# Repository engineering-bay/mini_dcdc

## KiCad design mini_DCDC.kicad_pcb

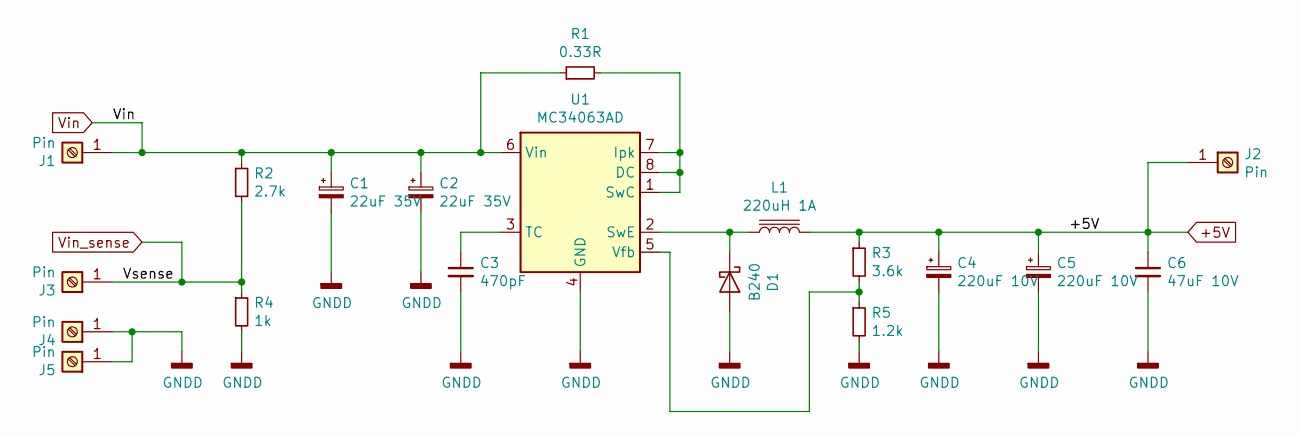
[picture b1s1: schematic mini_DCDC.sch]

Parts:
C1, C2: 22uF 35V; CP_EIA-7343-31_Kemet-D_Pad2.25x2.55mm_HandSolder; partnum 293D226X9035D2TE3
C3: 470pF; C_0805_2012Metric_Pad1.15x1.40mm_HandSolder; partnum CC0805JRNPO9BN471
C4, C5: 220uF 10V; CP_EIA-7343-31_Kemet-D_Pad2.25x2.55mm_HandSolder; partnum 293D227X9010D2TE3
C6: 47uF 10V; C_1206_3216Metric_Pad1.42x1.75mm_HandSolder; partnum GRM31CR61A476ME15L
D1: B240; D_SMB
J1, J2, J3, J4, J5: Pin; TestPoint_THTPad_2.0x2.0mm_Drill1.0mm
L1: 220uH 1A; SRR1208; partnum SRR1208-221KL
R1: 0.33R; R_0805_2012Metric_Pad1.15x1.40mm_HandSolder; partnum RL0805FR-070R33L
R2: 2.7k; R_0805_2012Metric_Pad1.15x1.40mm_HandSolder; partnum RC0805FR-0712KL
R3: 3.6k; R_0805_2012Metric_Pad1.15x1.40mm_HandSolder; partnum RC0805FR-072KL
R4: 1k; R_0805_2012Metric_Pad1.15x1.40mm_HandSolder; partnum RC0805FR-071KL
R5: 1.2k; R_0805_2012Metric_Pad1.15x1.40mm_HandSolder; partnum RC0805FR-071K2L
U1: MC34063AD; SOIC-8_3.9x4.9mm_P1.27mm

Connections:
+5V: C4.1, C5.1, C6.1, J2.1, L1.2, R3.1
GNDD: C1.2, C2.2, C3.2, C4.2, C5.2, C6.2, D1.2 (A), J4.1, J5.1, R4.2, R5.2, U1.4 (GND)
unnamed: C3.1, U1.3 (TC)
unnamed: D1.1 (K), L1.1, U1.2 (SwE)
unnamed: R1.2, U1.1 (SwC), U1.7 (Ipk), U1.8 (DC)
unnamed: R3.2, R5.1, U1.5 (Vfb)
Vin: C1.1, C2.1, J1.1, R1.1, R2.1, U1.6 (Vin)
Vin_sense: J3.1, R2.2, R4.1

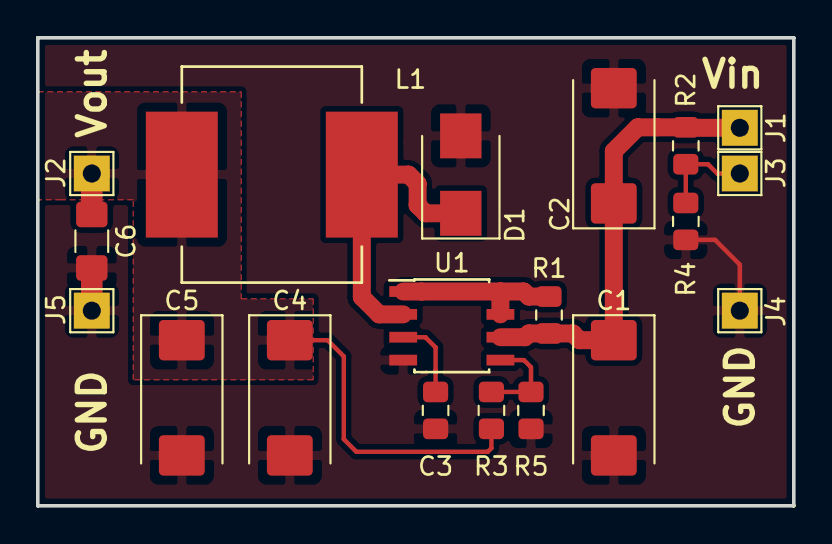
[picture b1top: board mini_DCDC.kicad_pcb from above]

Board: 2 copper layers, 42.0 x 26.0 mm, 19 parts (0 on the bottom side), 8 nets.

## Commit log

2019-06-05 Files added
2019-07-31 - Исправлена ошибка с неправильным подключением цепи обратной связи; - Увеличена длина платы на 2 мм; - Плата переразведена с учетом изменений в схеме;
